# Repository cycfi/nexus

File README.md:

# Nexus
The Nexus is a small, flexible, and hacker friendly breakout box that connects your multichannel guitar to the outside world using a specialized (LEMO compatible) multi-pin connector for up to 15 channels of audio and 7 channels of analog control voltages for by-wire (remote) control of volume, tone, patch or effects. Audio may come from standard mono-pickups or from the Nu multichannel pickup. Analog control voltages are converted to MIDI control messages.

Refer to this repository to get the Eagle libraries used in our schematic and pcb files: https://github.com/cycfi/eagle_common

Hardware design files licensed under a [Creative Commons Attribution-ShareAlike 4.0 International License](https://creativecommons.org/licenses/by-sa/4.0/).

Software source code distributed under the [MIT License](https://opensource.org/licenses/MIT).

http://www.cycfi.com/

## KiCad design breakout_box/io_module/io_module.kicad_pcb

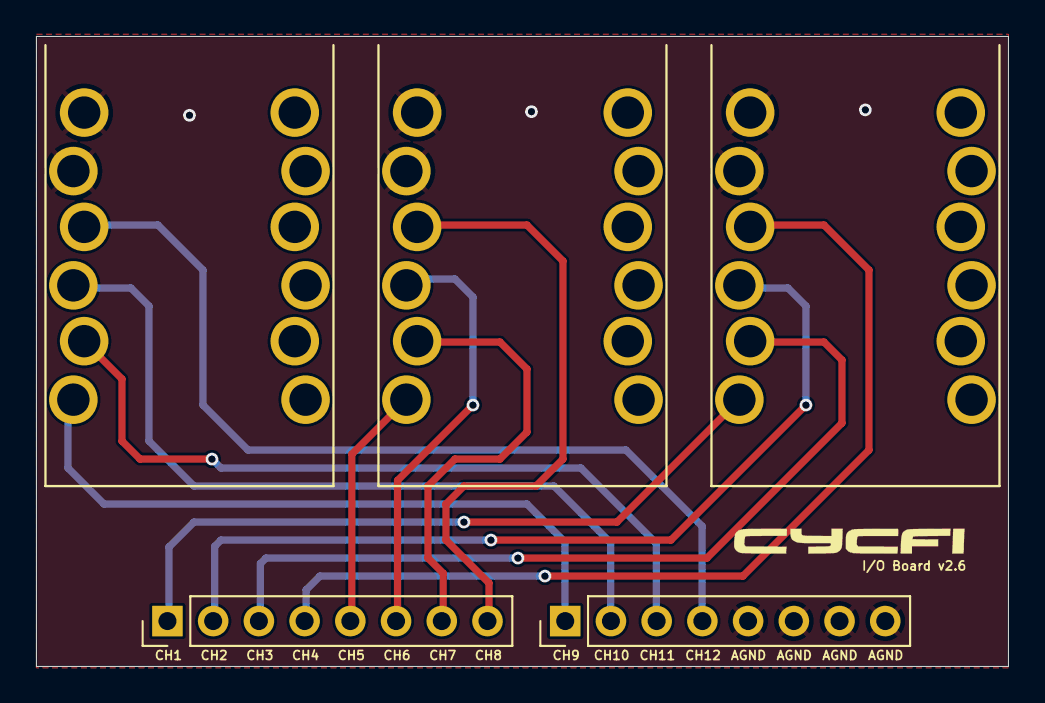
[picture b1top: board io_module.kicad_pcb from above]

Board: 2 copper layers, 54.0 x 35.0 mm, 5 parts (0 on the bottom side), 13 nets.

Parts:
H1, H2: MA08-1; PinHeader_1x08_P2.54mm_Vertical
J1, J2, J3: ZHEJINAG_CK_STSJACKS; ZHEJINAG_CK_6.35

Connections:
AGND: H2.5, H2.6, H2.7, H2.8, J1.2S (S), J1.S, J2.2S (S), J2.S, J3.2S (S), J3.S
CH1: H1.1, J1.2T (T)
CH2: H1.2, J1.2R (R)
CH3: H1.3, J1.T
CH4: H1.4, J1.R
CH5: H1.5, J2.2T (T)
CH6: H1.6, J2.2R (R)
CH7: H1.7, J2.T
CH8: H1.8, J2.R
CH9: H2.1, J3.2T (T)
CH10: H2.2, J3.2R (R)
CH11: H2.3, J3.T
CH12: H2.4, J3.R

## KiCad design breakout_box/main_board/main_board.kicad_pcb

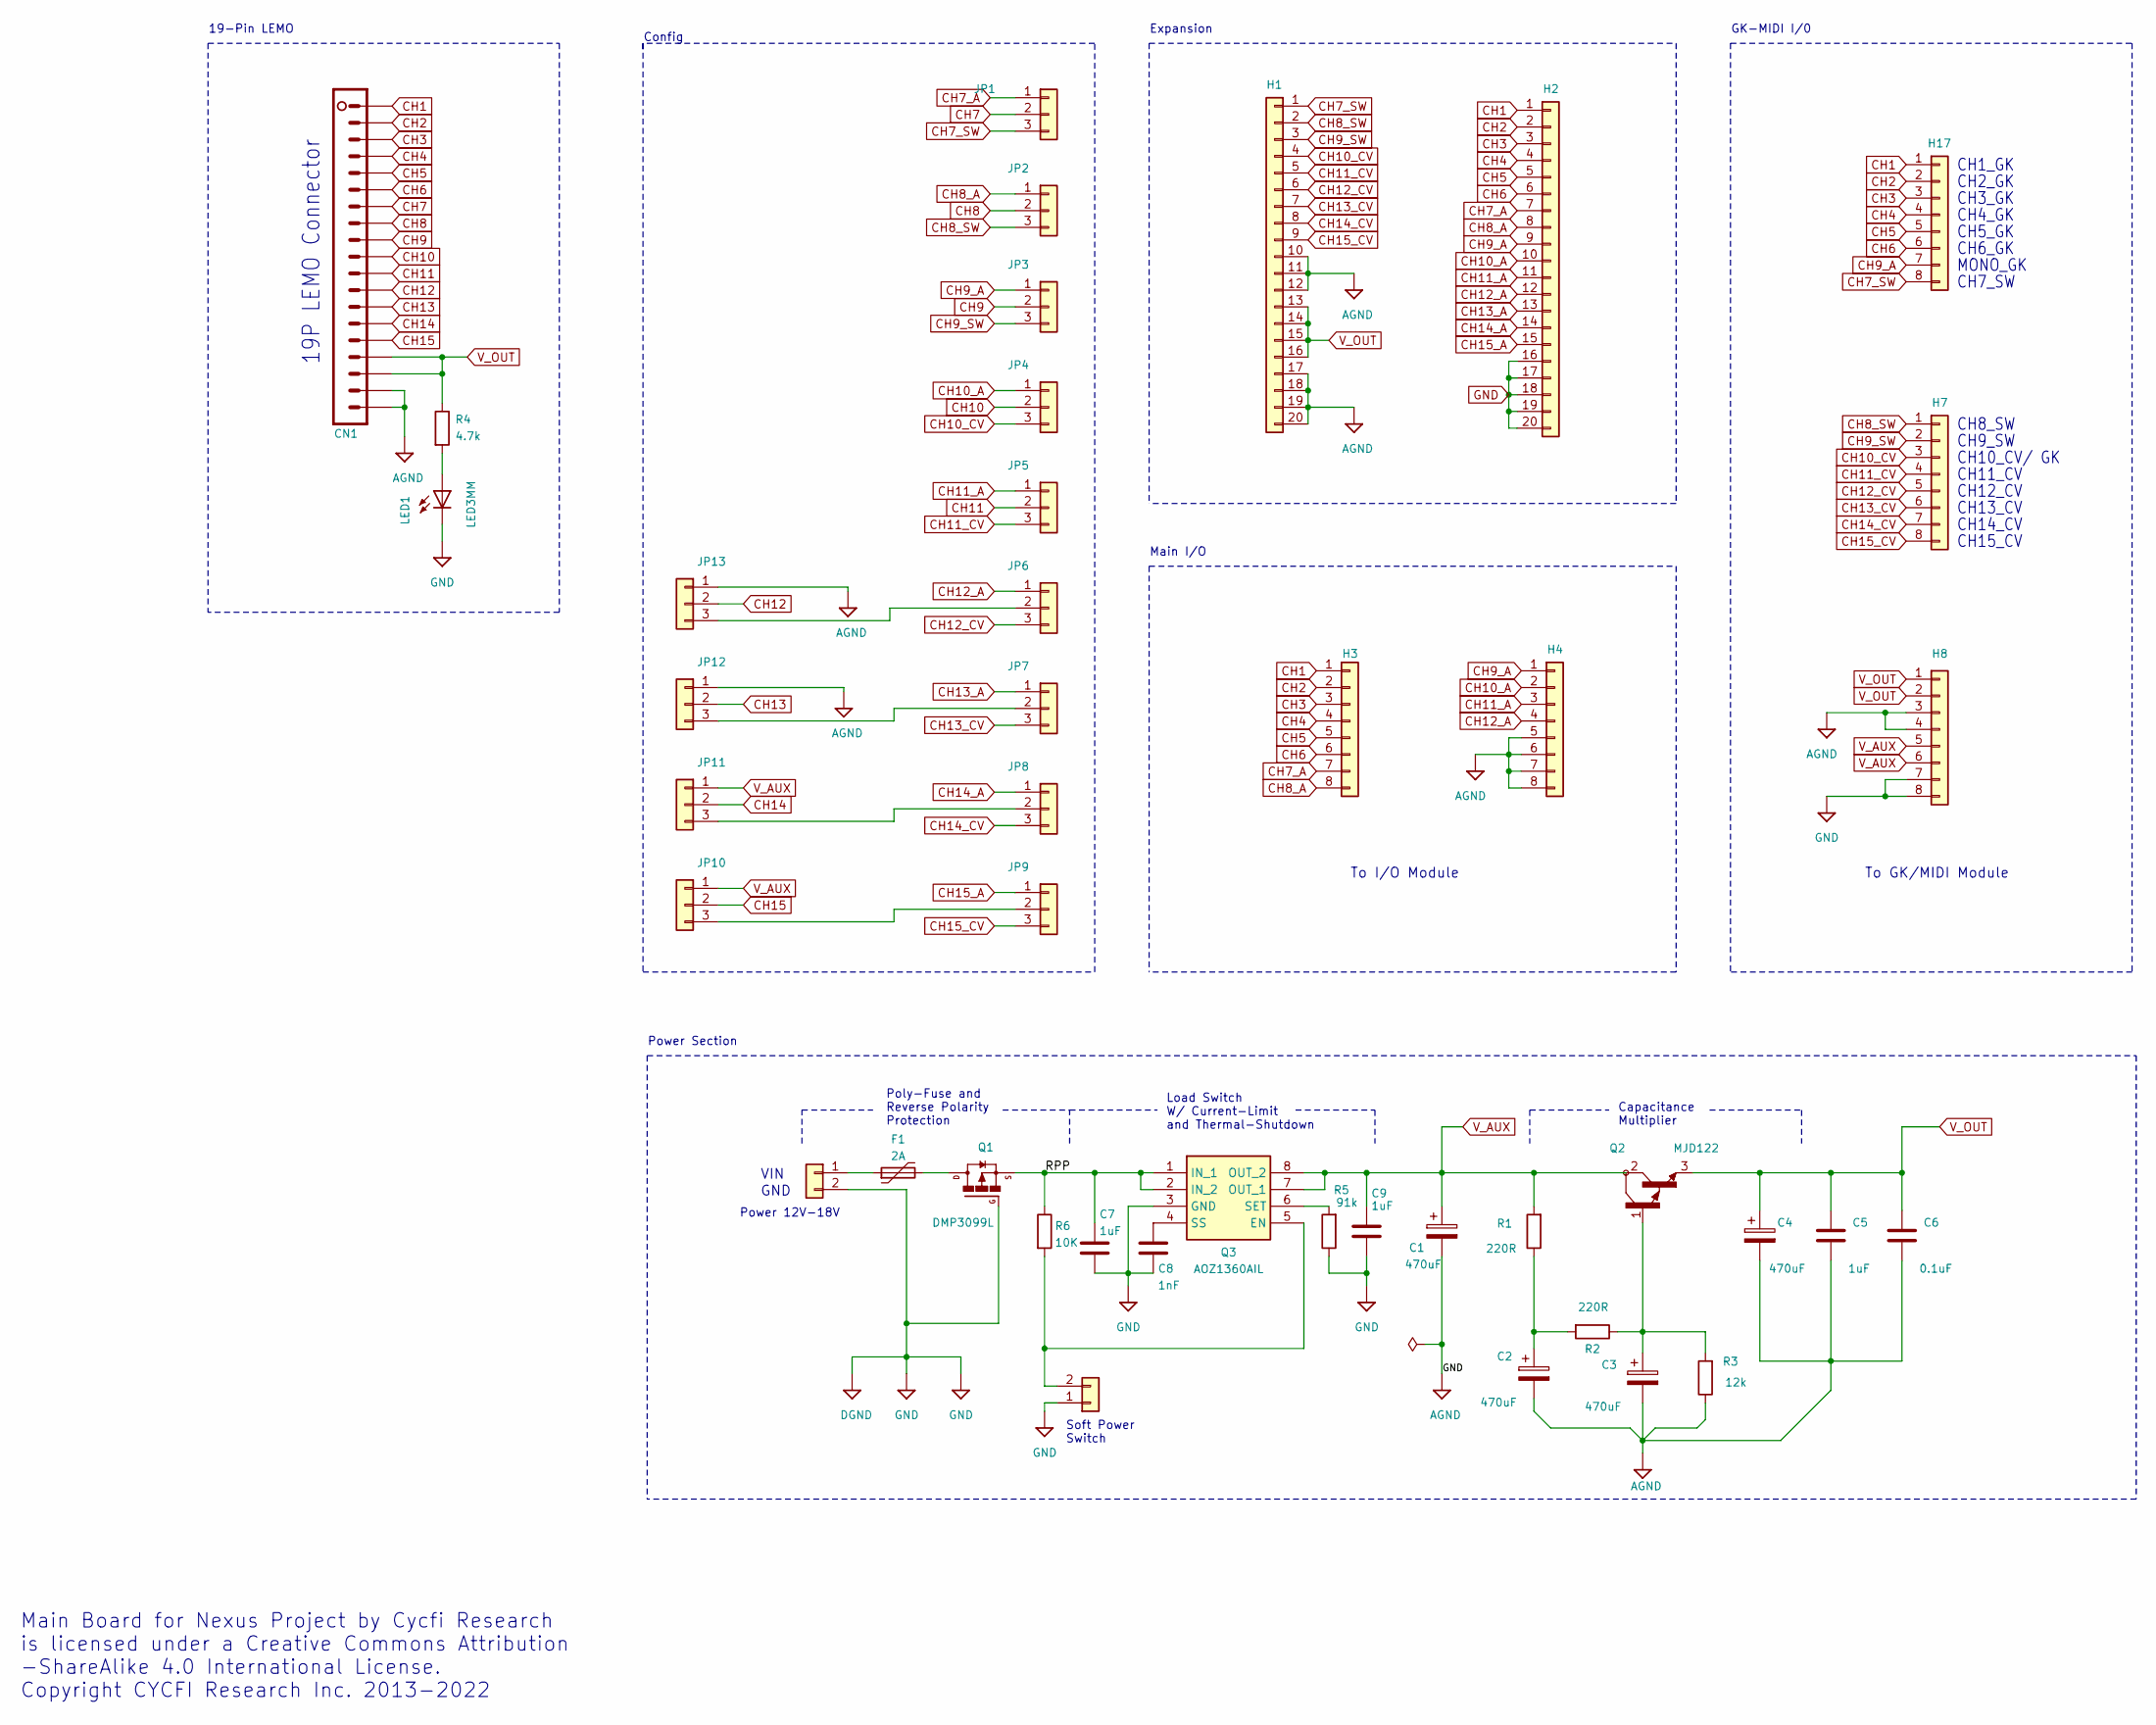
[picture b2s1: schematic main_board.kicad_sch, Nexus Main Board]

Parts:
C1, C2, C3, C4: 470uF; CP_Elec_10x10; LCSC C249933
C5, C7, C9: 1uF; C_0603_1608Metric; LCSC C15849
C6: 0.1uF; C_0603_1608Metric; LCSC C14663
C8: 1nF; C_0402_1005Metric; LCSC C1523
CN1: 19PIN_LEMO
F1: 2A; Fuse_1812_4532Metric; LCSC C883157
H1, H2: DNP; MA20-1
H3, H4, H7, H8, H17: MA08-1; PinHeader_1x08_P2.54mm_Vertical
H5: MA02-1; PinHeader_1x02_P2.54mm_Vertical
H6: MA02-1; PinHeader_1x02_P2.54mm_Horizontal
JP1, JP2, JP3, JP4, JP5, JP6, JP7, JP8, JP9, JP10, JP11, JP12, JP13: PINHD-1X03_2.00; 1X03M
LED1: LED3MM
Q1: DMP3099L; SOT-23; LCSC C2940610
Q2: MJD122; TO-252-2; LCSC C59488
Q3: AOZ1360AIL; SOIC127P600X175-8N; Manufacturer_Part_Number AOZ1360AIL; LCSC C146821
R1, R2: 220R; R_0603_1608Metric; LCSC C22962
R3: 12k; R_0603_1608Metric; LCSC C22790
R4: 4.7k; R_0805_2012Metric; LCSC C17673
R5: 91k; R_0603_1608Metric; LCSC C23265
R6: 10K; R_0402_1005Metric; LCSC C25744

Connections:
/RPP: C7.1, Q1.2 (S), Q3.1 (IN_1), Q3.2 (IN_2), R6.1
CH1: CN1.P$1 (1), H2.1, H3.1, H17.1
CH2: CN1.P$2 (2), H2.2, H3.2, H17.2
CH3: CN1.P$3 (3), H2.3, H3.3, H17.3
CH4: CN1.P$4 (4), H2.4, H3.4, H17.4
CH5: CN1.P$5 (5), H2.5, H3.5, H17.5
CH6: CN1.P$6 (6), H2.6, H3.6, H17.6
CH7: CN1.P$7 (7), JP1.2
CH7_A: H2.7, H3.7, JP1.1
CH7_SW: H1.1, H17.8, JP1.3
CH8: CN1.P$8 (8), JP2.2
CH8_A: H2.8, H3.8, JP2.1
CH8_SW: H1.2, H7.1, JP2.3
CH9: CN1.P$9 (9), JP3.2
CH9_A: H2.9, H4.1, H17.7, JP3.1
CH9_SW: H1.3, H7.2, JP3.3
CH10: CN1.P$10 (10), JP4.2
CH10_A: H2.10, H4.2, JP4.1
CH10_CV: H1.4, H7.3, JP4.3
CH11: CN1.P$11 (11), JP5.2
CH11_A: H2.11, H4.3, JP5.1
CH11_CV: H1.5, H7.4, JP5.3
CH12: CN1.P$12 (12), JP13.2
CH12_A: H2.12, H4.4, JP6.1
CH12_CV: H1.6, H7.5, JP6.3
CH13: CN1.P$13 (13), JP12.2
CH13_A: H2.13, JP7.1
CH13_CV: H1.7, H7.6, JP7.3
CH14: CN1.P$14 (14), JP11.2
CH14_A: H2.14, JP8.1
CH14_CV: H1.8, H7.7, JP8.3
CH15: CN1.P$15 (15), JP10.2
CH15_A: H2.15, JP9.1
CH15_CV: H1.9, H7.8, JP9.3
GND: C1.2, C2.2, C3.2, C4.2, C5.2, C6.2, C7.2, C8.2, C9.2, CN1.P$18 (18), CN1.P$19 (19), H1.10, H1.11, H1.12, H1.17, H1.18, H1.19, H1.20, H2.16, H2.17, H2.18, H2.19, H2.20, H4.5, H4.6, H4.7, H4.8, H5.1, H6.2, H8.3, H8.4, H8.7, H8.8, JP12.1, JP13.1, LED1.K (C), Q1.1 (G), Q3.3 (GND), R3.1, R5.1
unnamed: C2.1, R1.1, R2.2
unnamed: C3.1, Q2.1 (B), R2.1, R3.2
unnamed: C8.1, Q3.4 (SS)
unnamed: H5.2, Q3.5 (EN), R6.2
unnamed: F1.1, H6.1
unnamed: JP9.2, JP10.3
unnamed: JP8.2, JP11.3
unnamed: JP7.2, JP12.3
unnamed: JP6.2, JP13.3
unnamed: LED1.A, R4.2
unnamed: F1.2, Q1.3 (D)
unnamed: Q3.6 (SET), R5.2
V_AUX: C1.1, C9.1, H8.5, H8.6, JP10.1, JP11.1, Q2.2 (C), Q3.7 (OUT_1), Q3.8 (OUT_2), R1.2
V_OUT: C4.1, C5.1, C6.1, CN1.P$16 (16), CN1.P$17 (17), H1.13, H1.14, H1.15, H1.16, H8.1, H8.2, Q2.3 (E), R4.1

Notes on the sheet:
CH10_CV/ GK
CH3_GK
Main I/O
CH15_CV
To I/O Module
GK-MIDI I/0
Load Switch W/ Current-Limit and Thermal-Shutdown
CH12_CV
CH8_SW
Expansion
CH4_GK
CH7_SW
19-Pin LEMO
Power 12V-18V
CH13_CV
Capacitance Multiplier
CH14_CV
CH1_GK
CH5_GK
19P LEMO Connector
GND
CH6_GK
MONO_GK
CH11_CV
CH2_GK
Poly-Fuse and Reverse Polarity Protection
Main Board for Nexus Project by Cycfi Research is licensed under a Creative Commons Attribution -ShareAlike 4.0 International License. Copyright CYCFI Research Inc. 2013-2022
To GK/MIDI Module
CH9_SW
Soft Power Switch
VIN
Power Section
Config

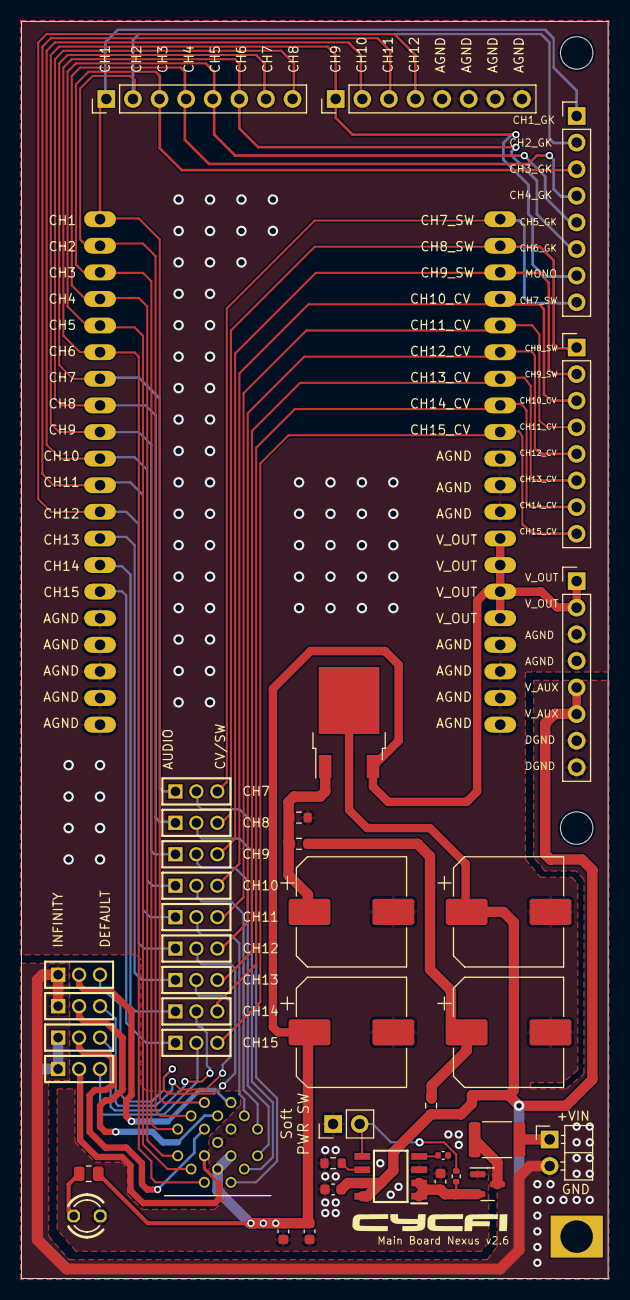
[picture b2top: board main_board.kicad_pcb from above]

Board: 2 copper layers, 56.0 x 120.0 mm, 46 parts (0 on the bottom side), 49 nets.

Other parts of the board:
@HOLE0, @HOLE0#2: (no value)
GND_HOLE: (no value)

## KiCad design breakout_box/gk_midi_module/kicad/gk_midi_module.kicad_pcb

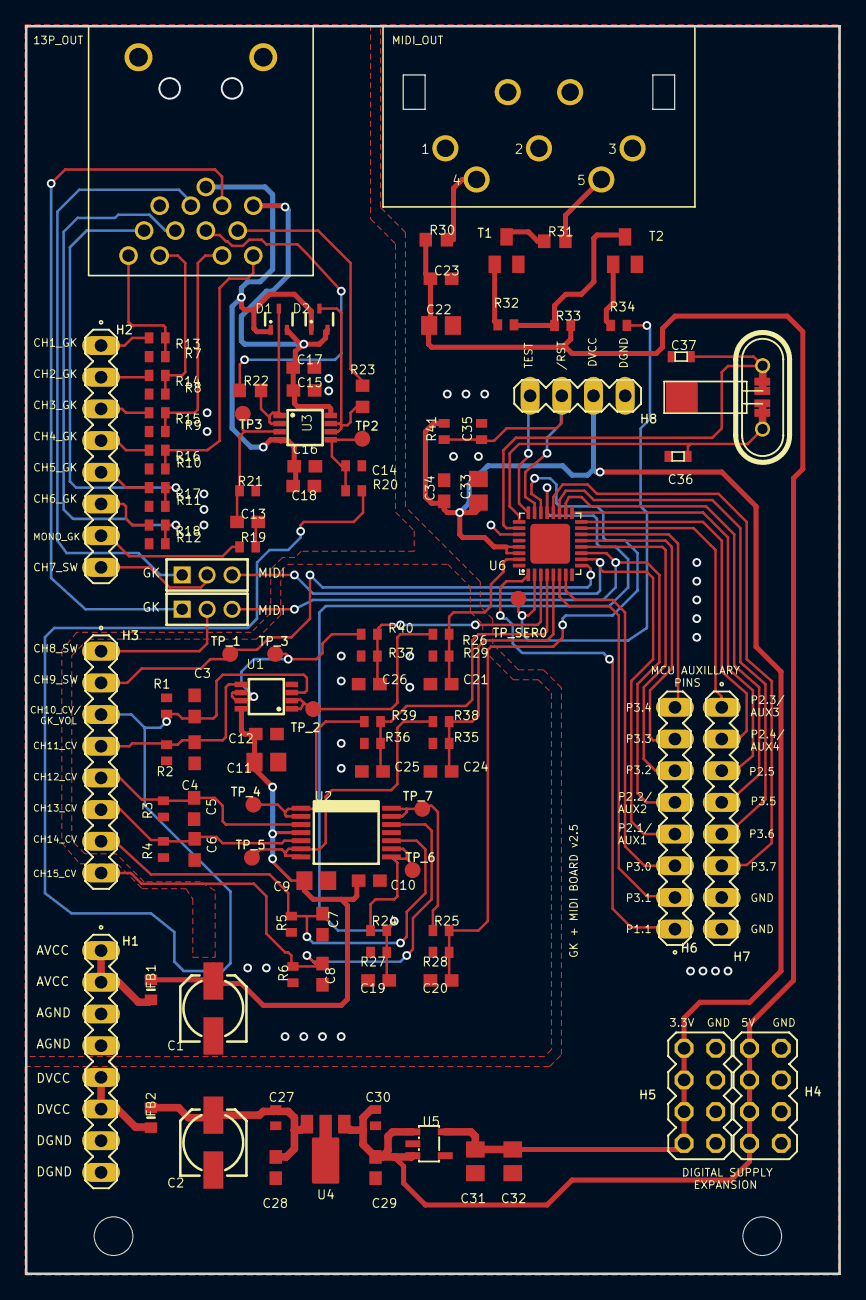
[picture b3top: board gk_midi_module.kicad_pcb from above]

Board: 2 copper layers, 65.2 x 100.0 mm, 115 parts (0 on the bottom side), 77 nets.

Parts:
@HOLE0, @HOLE1: (no value)
C1, C2: 100uF; 153CLV-0505
C3, C4, C5, C6, C7, C8, C10, C12, C17, C18, C19, C20, C21, C23, C24, C25, C26, C28, C29: 0.1uF; C0603
C9, C11, C22: 10uF; C0805
C13: 0.47uF; C0603
C14: 0.01uF; C0402
C15, C16: 4.7uF; C0603
C27, C30: 1uF; C0402
C31: 33uf; C0805
C32: 10uf; C0805
C33: 2.2uf; C0805
C34: 0.1uf; C0603
C35: 1nF; C0402
C36, C37: 12pF; 0603
D1, D2: 1SS302; SC70-3
FB1, FB2: BLM18KG700TN1D; BEADC1608X75N
H1, H2, H3: MA08-1
H4, H5: DNP; MA04-2
H6, H7: DNP; MA08-1
H8: MA04-1
JP2, JP3: 1X03M
MIDI1: MIDI_JACK
R1, R2, R3, R4, R5, R6: 100K; R0402
R7, R8, R9, R10, R11, R12, R13, R14, R15, R16, R17, R18, R24, R25, R26, R38, R39, R40: 5.1k; R0402
R19: 10K; R0402
R20: 18K; R0402
R21: 470K; R0402
R22, R23: 100R; R0603
R27, R28, R29, R35, R36, R37: 10k; R0402
R30, R31: 220; R0603
R32, R33, R34: 1K; R0402
R41: 47K; R0402
T1, T2: 2N2222; SOT23-3
TP2, TP3: TPB1,27; B1,27
TP_1, TP_2, TP_3, TP_4, TP_5, TP_6, TP_7: TPB1,27; B1,27
TP_SER0: TPB1,27; B1,27
U1: MSOP8
U2: LMV324; SSOP-14
U3: TLV2170DGKT; MSOP8
U4: L78LXX; SOT89
U5: MIC5205-3.3; SOT23-5
U6: MSP430G2553RHB32; QFN32
U$1: 13P_MIDI_2; 13P-MIDI-2
X1: QUARZ5

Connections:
+3.3V: C31.1, C32.1, C33.1, C34.1, H5.2, H5.4, H5.6, H5.8, H8.3, R41.1, U5.5, U6.29, U6.30
+5V: C22.1, C23.1, C29.1, C30.1, H4.2, H4.4, H4.6, H4.8, R30.1, R33.2, U4.1, U5.1, U5.3
+VE: C15.1, C17.1, D1.2, D2.2, U3.8, U$1.12
-VE: C16.2, C18.2, D1.1, D2.1, U3.4, U$1.13
AVCC: FB1.1, H1.1, H1.2
CH1_GK: H2.1, R7.2
CH2_GK: H2.2, R8.2
CH3_GK: H2.3, R9.2
CH4_GK: H2.4, R10.2
CH5_GK: H2.5, R11.2
CH6_GK: H2.6, R12.2
CH7_GK_SW: JP2.1, U$1.10
CH7_GK_SW/CV: H2.8, JP2.2
CH7_MIDI_SW: H6.4, JP2.3, U6.10
CH8_GK_SW: JP3.1, U$1.11
CH8_GK_SW/CV: H3.1, JP3.2
CH8_MIDI_SW: H6.5, JP3.3, U6.11
CH9_SW: H3.2, TP_1.TP, U6.9
CH10_CV: R26.1, TP_2.TP, U1.1, U1.2
CH10_GK_VOL: C3.1, H3.3, R1.2, R20.1, U1.3
CH11_CV: R40.2, TP_3.TP, U1.6, U1.7
CH12_CV: R39.2, TP_4.TP, U2.1, U2.2
CH13_CV: R38.2, TP_5.TP, U2.6, U2.7
CH14_CV: R24.1, TP_6.TP, U2.8, U2.9
CH15_CV: R25.1, TP_7.TP, U2.13, U2.14
CH15_CV_IN: C8.1, H3.8, R6.2, U2.12
DVCC: FB2.1, H1.5, H1.6
D_VIN: C2.+, C27.1, C28.1, FB2.2, U4.3
GK_VOL: R23.2, U$1.8
GND: C1.-, C2.-, C3.2, C4.2, C5.2, C6.2, C7.2, C8.2, C9.2, C10.2, C11.2, C12.2, C14.2, C15.2, C16.1, C17.2, C18.1, C19.2, C20.2, C21.2, C22.2, C23.2, C24.2, C25.2, C26.2, C27.2, C28.2, C29.2, C30.2, C31.2, C32.2, C33.2, C34.2, C35.2, C36.1, C37.1, H1.3, H1.4, H1.7, H1.8, H4.1, H4.3, H4.5, H4.7, H5.1, H5.3, H5.5, H5.7, H7.7, H7.8, H8.4, MIDI1.2, MIDI1.G1, MIDI1.G2, R1.1, R2.1, R3.1, R4.1, R5.1, R6.1, R13.1, R14.1, R15.1, R16.1, R17.1, R18.1, R21.2, R27.2, R28.2, R29.2, R35.2, R36.2, R37.2, T1.2, T2.2, U1.4, U2.11, U4.2, U4.2@1, U5.2, U6.27, U6.28, U$1.P$1, U$1.P$2, X1.GND@0
MONO_GK: H2.7, R19.1
unnamed: MIDI1.5, R31.2
unnamed: R31.1, T1.3
unnamed: R32.2, T1.1
unnamed: MIDI1.4, R30.2
unnamed: R34.2, T2.1
unnamed: R32.1, R33.1, T2.3
unnamed: C4.1, H3.4, R2.2, U1.5
unnamed: C5.1, H3.5, R3.2, U2.3
unnamed: C6.1, H3.6, R4.2, U2.5
unnamed: C7.1, H3.7, R5.2, U2.10
unnamed: R22.1, U$1.7
unnamed: D2.3, R23.1, U3.6, U3.7
unnamed: C14.1, R20.2, TP2.TP, U3.5
unnamed: C13.2, R19.2
unnamed: C13.1, R21.1, TP3.TP, U3.3
unnamed: D1.3, R22.2, U3.1, U3.2
unnamed: R7.1, R13.2, U$1.1
unnamed: R8.1, R14.2, U$1.2
unnamed: R9.1, R15.2, U$1.3
unnamed: R10.1, R16.2, U$1.4
unnamed: R11.1, R17.2, U$1.5
unnamed: R12.1, R18.2, U$1.6
P1.0: C21.1, R26.2, R29.1, U6.31
P1.1: H6.1, U6.1
P1.2: R34.1, TP_SER0.TP, U6.2
P1.3: C26.1, R37.1, R40.1, U6.3
P1.4: C25.1, R36.1, R39.1, U6.4
P1.5: C24.1, R35.1, R38.1, U6.5
P1.6: C19.1, R24.2, R27.1, U6.21
P1.7: C20.1, R25.2, R28.1, U6.22
P2.3: H7.1, U6.15
P2.4: H7.2, U6.16
P2.5: H7.3, U6.17
P2.6: C37.2, U6.26, X1.1
P2.7: C36.2, U6.25, X1.2
P3.0: H6.3, U6.7
P3.1: H6.2, U6.6
P3.2: H6.6, U6.12
P3.3: H6.7, U6.13
P3.4: H6.8, U6.14
P3.5: H7.4, U6.18
P3.6: H7.5, U6.19
P3.7: H7.6, U6.20
TEST: H8.1, U6.24
VIN: C1.+, C9.1, C10.1, C11.1, C12.1, FB1.2, U1.8, U2.4
~RST: C35.1, H8.2, R41.2, U6.23

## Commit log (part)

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2016-10-07 Documentation
2016-10-21 First commit, Energia software for MIDI
2016-10-31 updated using object-oriented programming
2016-11-07 separate main code from tests code
2016-11-07 working
2016-11-10 remove previous energia code folder
2016-11-11 Better MIDI code ported from cycfi msp430 lib to arduino.
2016-11-12 added pitch-bend
2016-11-12 - Very good analog tracking - Added fine adjustments
2016-11-12 Removed old files
2016-11-12 cleanup and refinements
2016-11-12 Added program change
2016-11-12 added program change up/down
2016-11-13 added button repeat
2016-11-13 group up, group down plus button repeat refinement
2016-11-13 complete implementation
2016-11-13 added persistence to flash
2016-11-13 Optimized save to miminize writing to flash
2016-11-13 faster save delay
2016-11-13 Added sysex and a way to dump the flash contents through sysex
2016-11-13 small tweaks
2016-12-05 Update license
2016-12-05 update some files
2016-12-05 remove caption
2016-12-07 *Edit Logo *Check BOM *Added 19P Connector Files
2016-12-08 CV Pot and CV Switch drawing pad and dxf files added
2016-12-08 modify license
2016-12-09 Added 19 Pin Lemo Elbow Connector PDF and DXF files
2016-12-15 Send MSB first, then and LSB.
2016-12-15 -commented some lines for actual testing of code -commented pitchbend function in main loop
2016-12-15 change low pass filter time constant from 256 to 64 change noise gate from 0 to 1
2016-12-29 removed unecessary NEXUS_DUMP_FLASH diagnostics
2017-01-04 -add important dimensions
2017-06-28 * analog_read function to compensate hardware design bug
2017-07-04 13P Breakout Eagle and BOM Files
2017-07-21 * analogRead adjustment
2017-08-30 added calibration for CV pot analog read isssue
2017-09-04 Updated BOM
2017-09-05 Updated copyright and document number of schematics
2017-09-05 Added 5 Way Switch to BOM
2017-09-05 Updated BOM, Copyright and Document Number
2018-08-14 test
2018-08-14 update main board (version_1.1)
2018-08-14 reupload midi module (version_1.0)
2018-08-14 update main board and midi module BOM
2018-08-14 reset devel
2018-08-17 create version 2.1 and update main and midi modules and delete nexyus cad drawings
2018-09-02 Update: Main Board MIDI Board MCU Board IO Board
    Delete:
    Mixer Board
2018-09-18 Slight Changes to MIDI and MCU: - Change BJT Part number on MIDI_Module - Delete Ferrite Bead on MCU_Module
2018-10-19 Change 10uF to 1uF in the schematics and BOM file
2018-10-23 Thin power traces on main board fixed
2018-10-25 Fixed power traces width
2019-03-05 Upload schematics for Main board v2.2
2019-03-05 Upload MIDI board for v2.2
2019-04-01 push dxf files for nexus' front and back panel
2019-04-02 add pdf files for nexus front and back panel
2019-04-16 Pushing CAD drawings for Nexus
2019-11-12 rename_files
2019-11-15 remove the common submodule
2019-11-15 folder renames
2019-11-15 more folder renames
2019-11-19 edit_readme
2020-02-05 commit and push eagle files for Nexus v2.3
2020-02-06 update boms and pdf for shematics files
2020-02-06 update shematic pdf
2020-05-28 Updates in Mainboard
2020-05-28 commit io board changes
2020-05-28 commit gk+midi board changes
2020-06-03 push pdf files of schematics
2020-06-03 remove outdated files
2020-06-08 update pullup on channel 9 and hysteresis fir channel 14
2020-06-15 updated midi source code, update hysterisis, update channel assignment
2020-06-20 update main board files
2020-06-20 update gk+midi files
2020-06-20 update board
2020-06-22 push Nexus peripheral files
2020-06-24 updates for 2 way switch
2020-06-29 Fixing Tim Noonan's bug report
2020-07-01 - Formatting changes indent=3 - Better distribution for putch-bend (from Tim Noonan)
2020-09-21 Update brd and sch file with corrected footprints
2020-09-22 upload bom files
2021-04-15 updated schematic and bom files for cv pot
2021-04-16 updated schematic, pcb layout and bom file
2021-04-16 add schematic and bom file
2021-04-29 Prototype channel mapping
2021-05-06 A bit more conservative
2021-05-06 Use 2nd order filter for faster response
2021-05-06 1kHz sync
2021-05-06 use 2-pole filter for pitch bend too.
2022-01-10 changed some resistors to 0603
2022-08-29 KiCAD version
2022-08-29 Clean update for KiCad
2022-08-29 Very clean port to KiCAD
2022-09-21 Main board updates
2023-02-24 PCB bug fix updates
2023-02-25 renames (don't use special symbols in file names).
2023-02-25 make the board perfectly rectangular
2023-03-05 Bump version to 2.6
2023-03-05 Upgrade to v2.6 - Added short circuit protection - Added soft power switch - Various schematics and PCB layout updates
2023-03-05 some tweaks
2023-03-06 Migrating I/O board to Kicad and updating to v2.6
2023-03-06 Added fabrication script
2023-03-06 PCB panel utilizing vcuts
2023-03-06 Change the component to C2977785, plus various PCB refinements
2023-04-08 Use AOZ1360AIL load switch
2023-04-10 Updates for PCBA and panelization
2023-11-07 the hex file for flashing
2025-05-08 Kicad import from Eagle
2025-11-24 Kicad updated this
2026-01-09 Added latest GK-MIDI module fabrication files taken from "GK-MIDI January 2024 JLCPCB"
2026-02-09 Generated PDF
2026-04-08 Preparation before merge to master
2026-04-08 remove outdated comment
2026-04-08 Ignore the test build stuff
2026-04-08 We need then gate!
2026-04-08 Remove unused initializer
2026-04-08 Switch to a DC/Offset servo that tracks offsets only near the deadband window
2026-04-08 Use time based blanking for the pitch bend controller: only accept pitch bend if the previous reading is within a few milliseconds in the past. This will eliminate one-offs, but that does not happen 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
2026-04-09 We're getting there... still optimizing.
2026-04-09 pre-warm the controllers at startup
2026-04-09 Reset the code pre enhancements.
2026-04-09 - Primed the CC controllers - Reverted the oversampling code
2026-04-09 remove the moving average filter. it's not needed anymore.
2026-04-09 Cleanup: remove gate with hysteresis. it's not needed.
2026-04-09 - Cleanup and remove old unmaintained test code - Latest binary
2026-04-10 Replace the old change-tracking gate with a true zero-centered dead-zone gate for pitch bend, while keeping delta-based thresholding only for unipolar CC movement detection.
2026-04-10 Make startup blanking one-shot and fix near-center pitch bend behavior
2026-04-10 Refactor pitch bend processing into smaller helper functions
2026-04-10 add comments that explain the behavior of the handle_startup_blank() function
2026-04-10 Switch MIDI output smoother from lowpass to moving_average
    Replace pb_out_lp (lowpass<8>, TC≈8ms) with pb_out_ma
    (moving_average<2>, N=4, 4ms window) for smoothing the gate
    open/close transitions and interpolating between discrete LP
    limit-cycle steps. The MA gives a cleaner, more uniform
    impulse response that produces visually smooth vibrato curves
    with no staircasing or chatter at the zero crossing.
2026-04-10 Various cleanup
2026-04-11 Remove the post filter. It does not help much.
2026-04-11 Simplify pitch bend controller
2026-04-11 Blank pitch bend during CC movement
2026-04-11 Add pitch bend centering servo
2026-04-11 Emit trailing pitch bend center
2026-04-12 Document pitch bend controller behavior
2026-04-13 Stabilize MIDI controller startup and endpoints
    Add raw-domain hysteresis before quantizing analog CC inputs to 7-bit MIDI values, so endpoint noise does not chatter between adjacent CC values. Snap and hold the 0/127 endpoints with a release band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
    Keep pitch bend muted during startup until the centered signal has remained stable for two seconds, preventing noisy boards from arming a small bend while the Hall/reference path settles. Raise the p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
2026-04-13 Refine pitch bend startup guard
    Remove the timed startup blanking that could leave the whammy feeling unresponsive after boot.
    Replace it with a one-shot center guard that mutes only near-center startup drift until the first real whammy movement, then falls back to the normal narrow center window so vibrato crossings are not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
2026-04-14 Clarify pitch bend center handling
    Extract the return-to-center dwell logic from the main pitch bend update path so operator() reads as a sequence of state transitions: center dwell, startup guard, delta-gate arming, and active output.
    Mark the center helper routines static because they do not depend on per-instance state, and add comments around the non-obvious startup and arming behavior.
2026-04-14 Publish MIDI controller state at startup
    Send the seeded startup state for analog CC controllers and sustain during initialization, while keeping pitch bend neutral at center.
    Seed the sustain edge detector from the startup switch state so the explicit initial sustain message is not followed by a duplicate debounce edge.
    Program change and bank select continue to use their persisted flash state and existing transmit path. Energia build verified before commit.
2026-04-16 io_module fab updates; update to latest kicad
2026-04-24 Re-added BOM
2026-04-24 Remove redundant 'post'
2026-06-27 nexus_midi: CMake build + control extraction + host test harness
    Standalone CMake build (reuses the Energia-bundled msp430-gcc, byte-equivalent to the IDE build); control logic extracted from the .ino into nexus_controls.hpp behind a raw_adc() ADC seam; a NEXUS_SI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
    Granular history preserved on the feature branches.
2026-06-27 nexus_midi: pitch-bend center-stability (feed-forward predictor)
    Clean-room digital port of the eWhammy analog center-stability, then evolved past it: the spring-return hysteresis is COMPUTED from the deflection (feed-forward predictor off a fixed seed) rather tha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
    Granular dev history (reactive servo, k-learning experiment, etc
2026-06-27 nexus_midi: decompose pitch_bend_controller into unit-tested blocks
    Eight processor blocks, each unit-tested: the general ones (slew_gate, stillness, dc_servo, dynamic_smoother, moving_average_n) to util.hpp as templates; the pitch-specific ones (hysteresis_predictor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
    Per-block granular history on the center-stability-refactor branch.
2026-06-27 nexus_midi: correct note 1 -- the removed k-learner sampled the output
    It read corrected (post-servo, post-prediction), which the servo had already nulled, so it never saw the error -- not 'a wash' for no reason. Learning belongs in the input domain (dev_m); see KB k_le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
2026-06-28 nexus_midi: inertial_corrector center-stability (slope hang-land + 10 s watchdog)
    Squash of the center-stability branch (10 commits). Replaces the feed-forward
    predictor / k_learner / post_corrector / center_detent with a single
    inertial_corrector: a noise-gated hang-lander that nulls a stalled release to
    center via low-passed slope detection (snappy ~150 ms snap), plus a
    freeze_watchdog that flushes an output stuck off-center for 10 s (the
    programmer-disconnect reference-shift backstop). Dead code removed; the
2026-06-29 nexus_midi: merge center-stability landing refinements (squash) + refresh image
    Squash of the center-stability landing work onto master: the vigor-adaptive
    exponential hang-land (peak-slope sized, slope/tau clamped, never-cross-center
    clamp) and the 1 ST -> 4 ST audibility-aligned arm threshold. Refreshes the
    prebuilt no-diag production image nexus_midi.hex (.text 9520, diag OFF).
2026-06-29 nexus_midi: format all source to the 77-column convention
    Comments / formatting only -- binary unchanged (.text 9520, host_sim 11/11).
    Wraps every source file to <= 77 cols (prose, function comments, and trailing
    comments alike; long member types aliased via typedef for the device GCC 4.6).
    Fixes the stale +/-1 ST arm references to +/-4 ST. Normalizes the decorative
    full-width dividers to 80 cols. Adds the blank-line spacing (one empty line
    after a paragraph, and between multi-line list items). Files: nexus_controls,
